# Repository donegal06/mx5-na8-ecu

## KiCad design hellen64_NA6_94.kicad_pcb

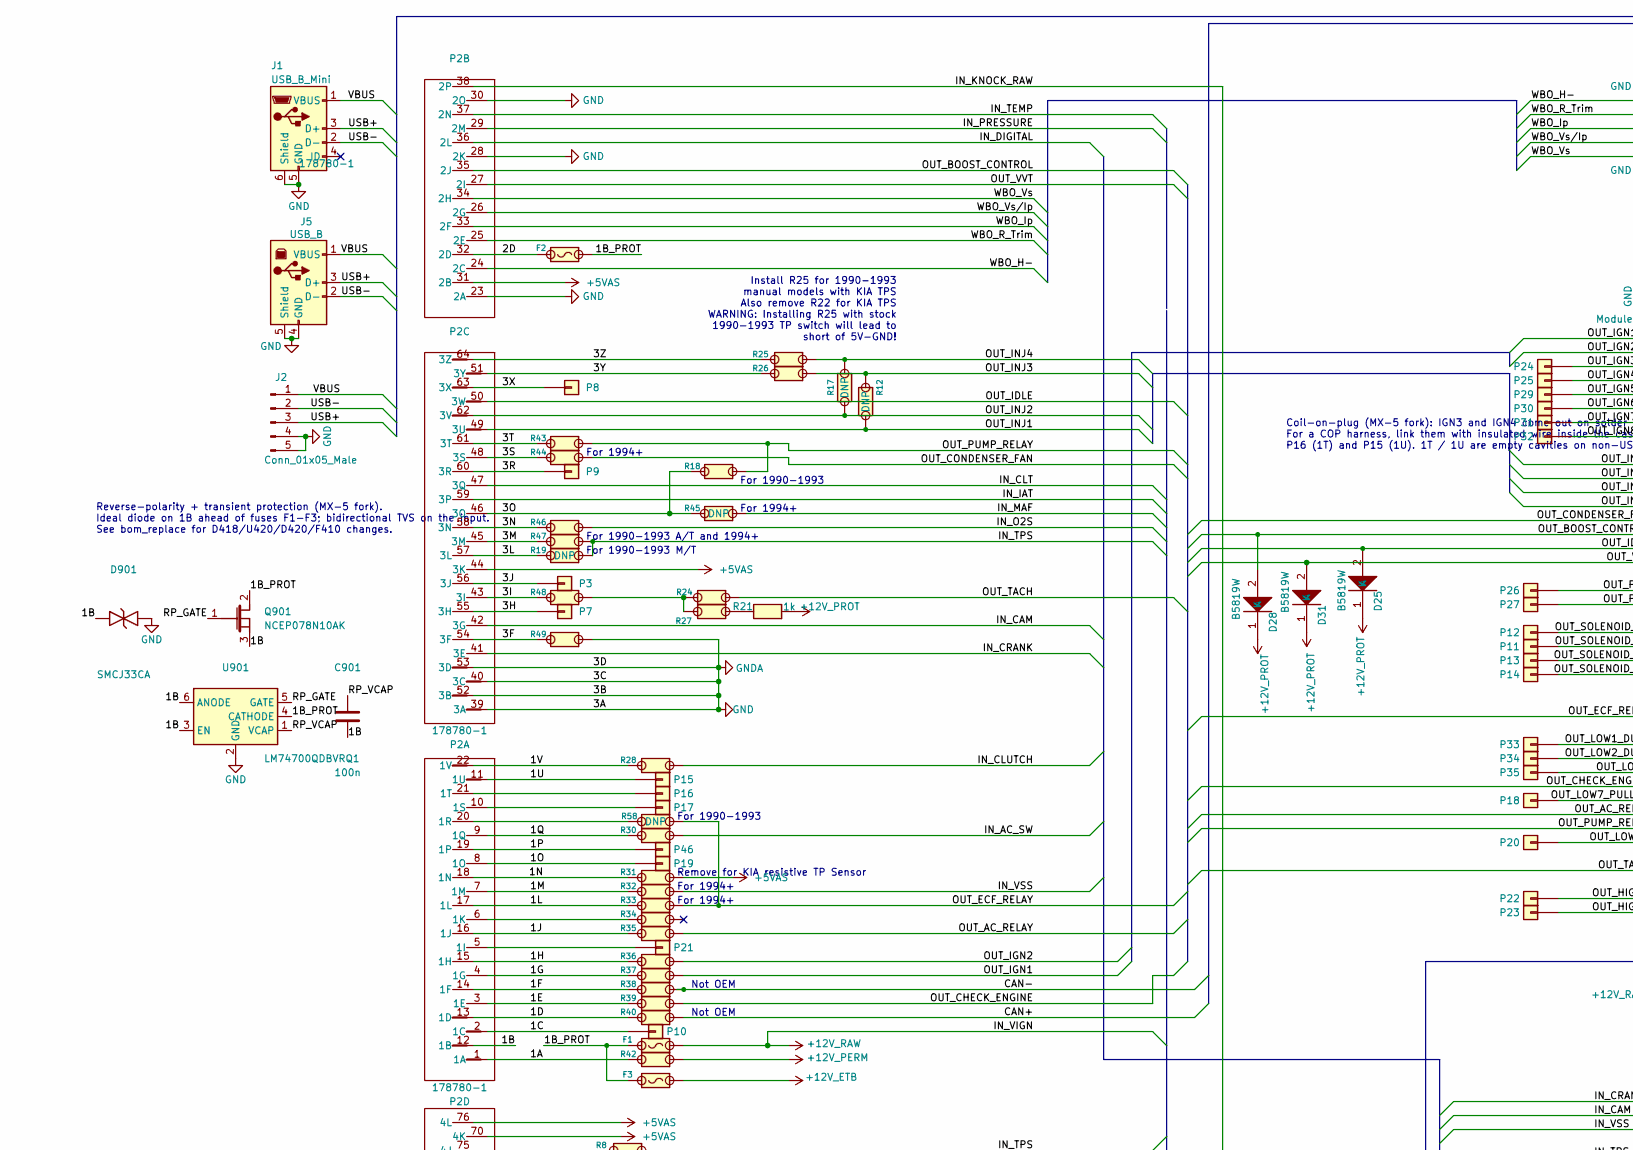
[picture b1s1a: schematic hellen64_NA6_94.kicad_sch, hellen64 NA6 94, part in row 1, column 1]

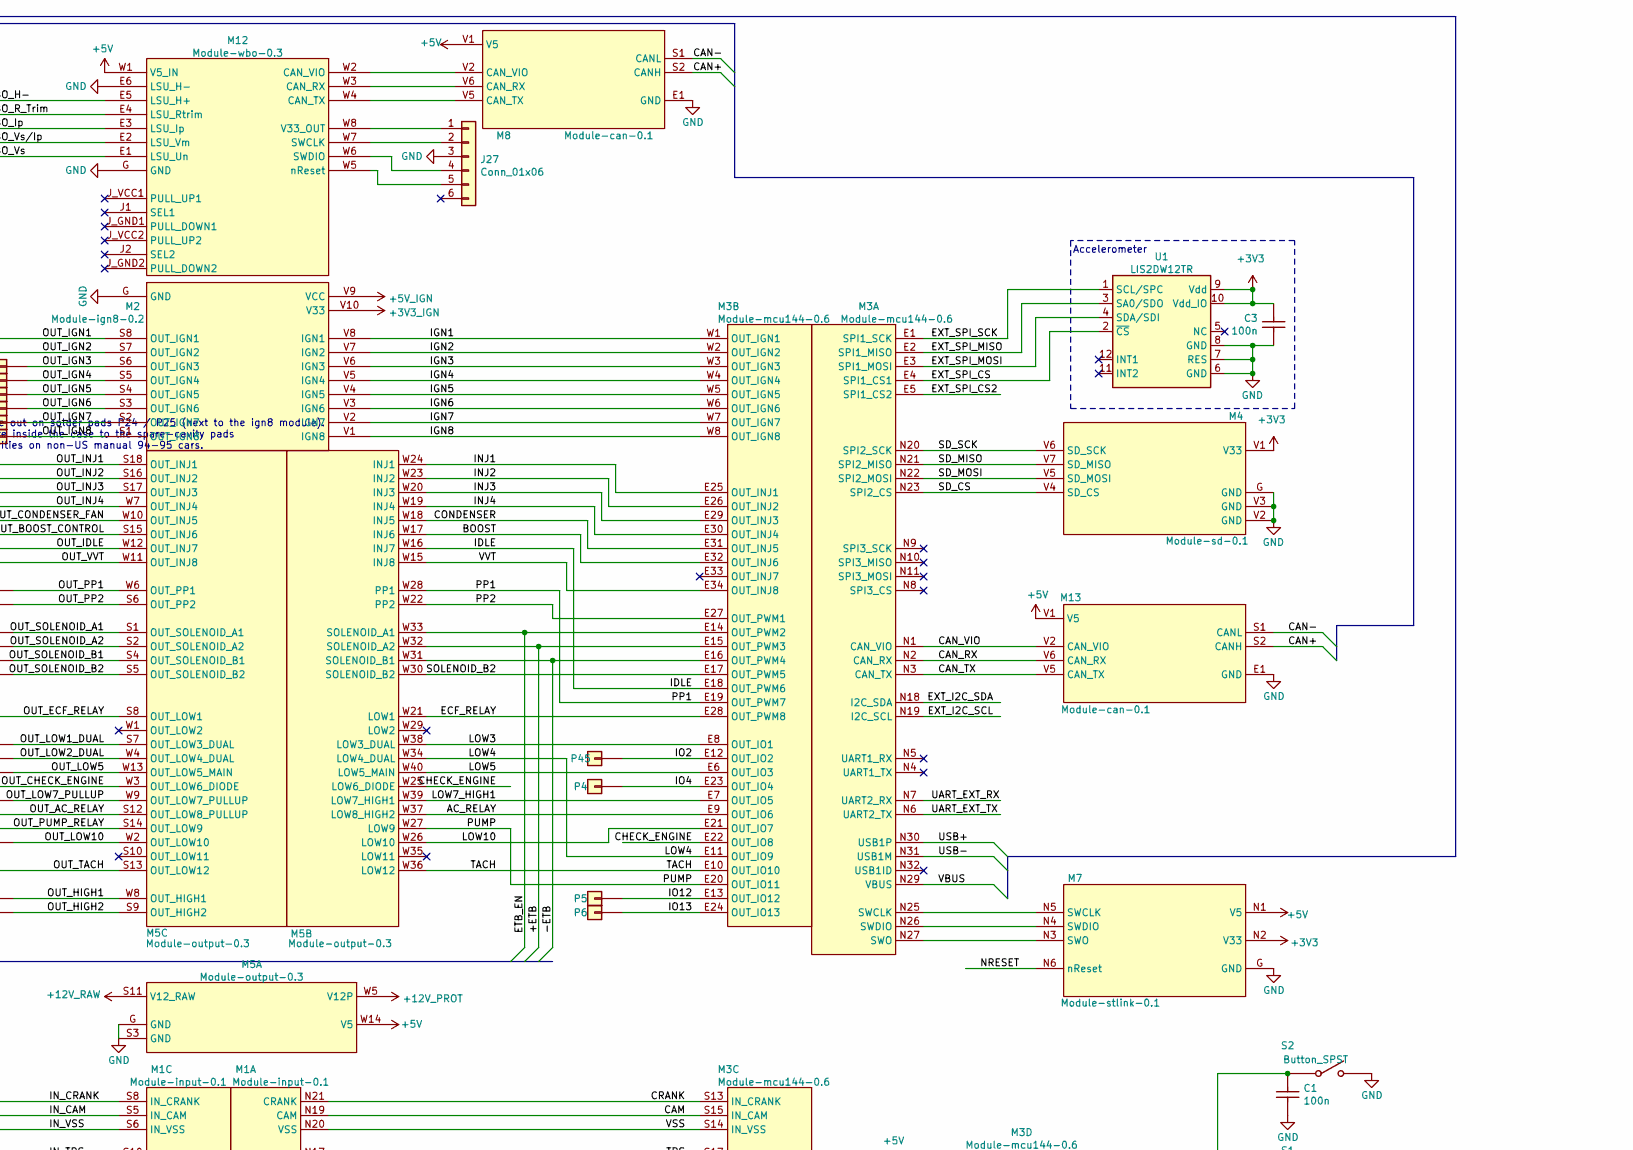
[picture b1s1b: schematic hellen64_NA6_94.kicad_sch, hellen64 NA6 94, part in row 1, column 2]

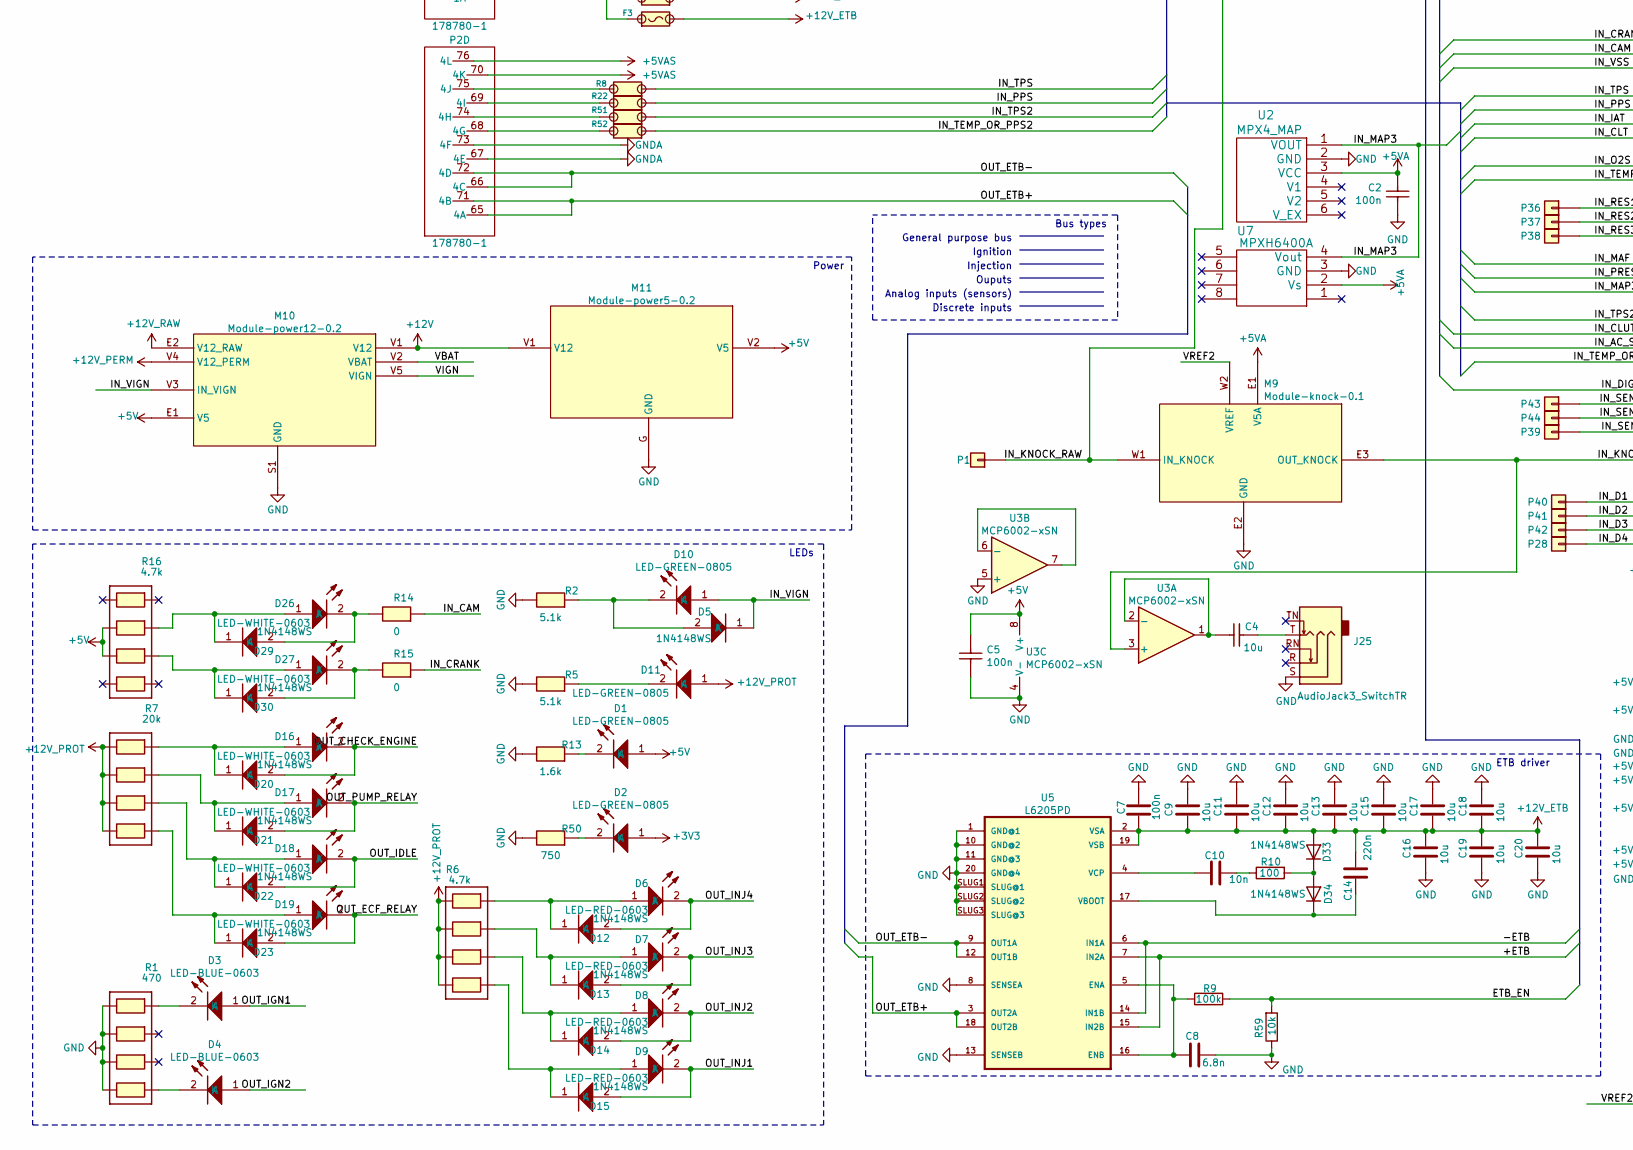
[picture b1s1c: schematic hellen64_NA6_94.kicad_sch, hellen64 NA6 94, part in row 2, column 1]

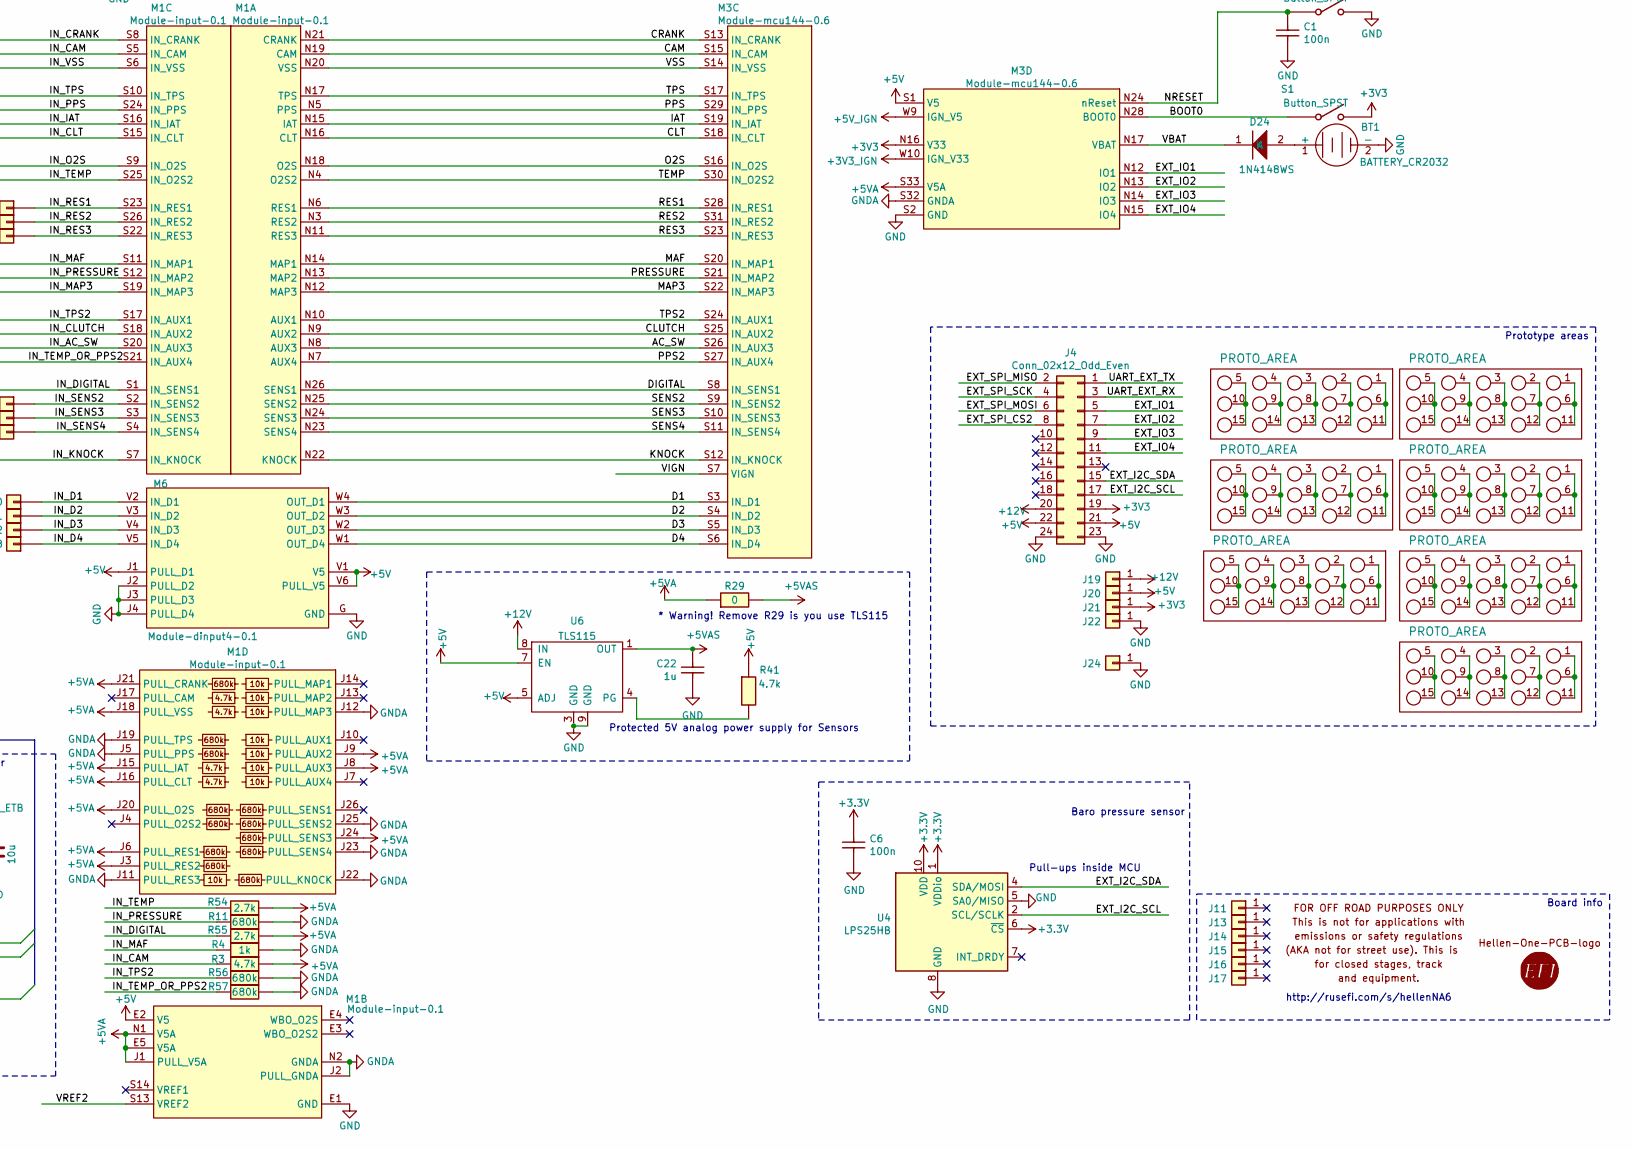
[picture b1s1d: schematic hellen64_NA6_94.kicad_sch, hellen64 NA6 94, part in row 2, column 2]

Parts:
BT1: BATTERY_CR2032; BatteryHolder_Keystone_1060_1x2032; LCSC C70377
C1, C2, C3, C5, C6, C7, C901: 100n; C0603; LCSC C14663
C4: 10u; C0603; LCSC C19702
C8: 6.8n; C0603; LCSC C1631
C9, C11, C12, C13, C15, C16, C17, C18, C19, C20: 10u; C0805; LCSC C15850
C10: 10n; C0603; LCSC C57112
C14: 220n; C0603; LCSC C21120
C22: 1u; C0603; LCSC C15849
D1, D2, D10, D11: LED-GREEN-0805; LED-0805; LCSC C2297
D3, D4: LED-BLUE-0603; LED-0603; LCSC C72041
D5, D12, D13, D14, D15, D20, D21, D22, D23, D24, D29, D30, D33, D34: 1N4148WS; SOD-323; LCSC C2128
D6, D7, D8, D9: LED-RED-0603; LED-0603; LCSC C2286
D16, D17, D18, D19, D26, D27: LED-WHITE-0603; LED-0603; LCSC C2290
D25, D28, D31: B5819W; SOD-123; LCSC C8598
D901: SMCJ33CA; D_SMC; LCSC C699040
F1, F2, F3: Fuse-Pad-Pad; PAD-1206-PAD; LCSC C182446
G1, G3: LOGO
G2: DISCLAIMER; Off_Road_Disclaimer
G4, G5, G6, G7, G9, G11, G12: PROTO_AREA
J1: USB_B_Mini; USB-MINI-B-VERTICAL; LCSC C13453
J2: Conn_01x05_Male; Molex_SPOX_5267-05A_1x05_P2.50mm_Vertical
J4: Conn_02x12_Odd_Even; PinHeader_2x12_P2.54mm_Vertical
J5: USB_B; LCSC C46392
J11, J13, J14, J15, J16, J17: Conn_01x01; MountingHole_4.5mm_Pad
J19, J20, J21, J22, J24: Conn_01x01; TestPoint_Pad_D2.0mm
J25: AudioJack3_SwitchTR; Jack_3.5mm_PJ-3250-5A; LCSC C165947
J27: Conn_01x06; PinHeader_1x06_P2.54mm_Vertical
M1: Module-input-0.1; input
M2: Module-ign8-0.2; ign8
M3: Module-mcu144-0.6; mcu
M4: Module-sd-0.1; sd
M5: Module-output-0.3; output
M6: Module-dinput4-0.1; dinput4
M7: Module-stlink-0.1; stlink
M8, M13: Module-can-0.1; can
M9: Module-knock-0.1; knock
M10: Module-power12-0.2; power12
M11: Module-power5-0.2; power5
M12: Module-wbo-0.3; wbo
P1, P3, P4, P5, P6, P7, P8, P9, P10, P11, P12, P13, P14, P15, P16, P17, P18, P19, P20, P21, P22, P23, P24, P25, P26, P27, P28, P29, P30, P31, P32, P33, P34, P35, P36, P37, P38, P39, P40, P41, P42, P43, P44, P45, P46: Pad; PAD-TH
P2: 178780-1
Q901: NCEP078N10AK; TO-252-2; LCSC C2686699
R1: 470; R0603-4; LCSC C25510
R2, R5: 5.1k; R0603; LCSC C23186
R3, R41: 4.7k; R0603; LCSC C23162
R4, R21: 1k; R0603; LCSC C21190
R6, R16: 4.7k; R0603-4; LCSC C1980
R7: 20k; R0603-4; LCSC C12004
R8, R18, R22, R24, R25, R26, R27, R28, R30, R31, R32, R33, R34, R35, R36, R37, R38, R39, R40, R42, R43, R44, R46, R47, R48, R49, R51, R52: Jumper-Pad-Pad; PAD-0805-PAD; LCSC C17477
R9: 100k; R0603; LCSC C25803
R10: 100; R0603; LCSC C22775
R11, R56, R57: 680k; R0603; LCSC C25822
R12, R17, R19, R45, R58: Jumper-Pad-Pad; PAD-0805-PAD
R13: 1.6k; R0603; LCSC C22847
R14, R15: 0; R0603; LCSC C21189
R29: SMD1206B035TF/16; R1206; LCSC C269114
R50: 750; R0603; LCSC C23241
R54, R55: 2.7k; R0603; LCSC C13167
R59: 10k; R0603; LCSC C25804
S1, S2: Button_SPST; SMD-2_2.9x3.9x1.7; LCSC C115357
U1: LIS2DW12TR; LGA-12_2x2mm_P0.5mm; LCSC C189624
U2: MPX4_MAP; MPX-4_MAP
U3: MCP6002-xSN; SOIC-8_3.9x4.9mm_P1.27mm; LCSC C7377
U4: LPS25HB; ST_HLGA-10_2.5x2.5mm_P0.6mm_LayoutBorder3x2y; LCSC C87898
U5: L6205PD; SO20POWER; LCSC C36543
U6: TLS115; PG-DSO-8-43; LCSC C540242
U7: MPXH6400A; MPXH6400A-SSOP8; LCSC C511770
U901: LM74700QDBVRQ1; SOT-23-6; LCSC C2941042

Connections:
+3V3_IGN: M2.V10 (V33), M3.W10 (IGN_V33)
+5V: C5.2, D1.1 (A), J4.21, J4.22, J20.1, M1.E2 (V5), M3.S1 (V5), M5.W14 (V5), M6.J1 (PULL_D1), M6.V1 (V5), M6.V6 (PULL_V5), M7.N1 (V5), M8.V1 (V5), M10.E1 (V5), M11.V2 (V5), M12.W1 (V5_IN), M13.V1 (V5), R16.2, R16.3, R41.1, U3.8 (V+), U6.5 (ADJ), U6.7 (EN)
+5VA: C2.2, M1.E5 (V5A), M1.J1 (PULL_V5A), M1.J3 (PULL_RES2), M1.J6 (PULL_RES1), M1.J8 (PULL_AUX3), M1.J9 (PULL_AUX2), M1.J15 (PULL_IAT), M1.J16 (PULL_CLT), M1.J18 (PULL_VSS), M1.J20 (PULL_O2S), M1.J21 (PULL_CRANK), M1.J24 (PULL_SENS3), M1.N1 (V5A), M3.S33 (V5A), M9.E1 (V5A), R3.1, R29.1, R54.2, R55.2, U2.3 (VCC), U7.2 (Vs)
+5VAS: C22.2, P2.31 (2B), P2.44 (3K), P2.70 (4K), P2.76 (4L), R29.2, R31.1, U6.1 (OUT)
+5V_IGN: M2.V9 (VCC), M3.W9 (IGN_V5)
+12V: J4.20, J19.1, M10.V1 (V12), M11.V1 (V12), U6.8 (IN)
+12V_ETB: C7.2, C9.1, C11.1, C12.1, C13.1, C14.1, C15.1, C16.2, C17.1, C18.1, C19.2, C20.2, D33.2 (A), F3.2, U5.2 (VSA), U5.19 (VSB)
+12V_PERM: M10.V4 (V12_PERM), R42.1
+12V_PROT: D11.1 (A), D25.1 (K), D28.1 (K), D31.1 (K), M5.W5 (V12P), R6.1, R6.2, R6.3, R6.4, R7.1, R7.2, R7.3, R7.4, R21.1
+12V_RAW: D5.1 (K), D10.1 (A), F1.2, M5.S11 (V12_RAW), M10.E2 (V12_RAW), M10.V3 (IN_VIGN)
/1A: P2.1 (1A), R42.2
/1B: C901.2, D901.1 (A1), P2.12 (1B), Q901.3 (S), U901.3 (EN), U901.6 (ANODE)
/1B_PROT: F1.1, F2.2, F3.1, Q901.2 (D), U901.4 (CATHODE)
/1C: P2.2 (1C), P10.1
/1D: P2.13 (1D), R40.2
/1E: P2.3 (1E), R39.2
/1F: P2.14 (1F), R38.2
/1G: P2.4 (1G), R37.2
/1H: P2.15 (1H), R36.2
/1J: P2.16 (1J), R35.2
/1L: P2.17 (1L), R33.2
/1M: P2.7 (1M), R32.2
/1N: P2.18 (1N), R31.2
/1O: P2.8 (1O), P19.1
/1P: P2.19 (1P), P46.1
/1Q: P2.9 (1Q), R30.2
/1U: P2.11 (1U), P15.1
/1V: P2.22 (1V), R28.2
/2D: F2.1, P2.32 (2D)
/3F: P2.54 (3F), R49.2
/3H: P2.55 (3H), P7.1
/3I: P2.43 (3I), R48.2
/3J: P2.56 (3J), P3.1
/3L: P2.57 (3L), R19.2
/3M: P2.45 (3M), R47.2
/3N: P2.58 (3N), R46.2
/3O: P2.46 (3O), R18.2, R45.2
/3R: P2.60 (3R), P9.1
/3S: P2.48 (3S), R44.2
/3T: P2.61 (3T), R43.2
/3X: P2.63 (3X), P8.1
/3Y: P2.51 (3Y), R26.2
/3Z: P2.64 (3Z), R25.2
/+ETB: M3.E15 (OUT_PWM3), M5.W32 (SOLENOID_A2), U5.7 (IN2A), U5.15 (IN2B)
/-ETB: M3.E16 (OUT_PWM4), M5.W31 (SOLENOID_B1), U5.6 (IN1A), U5.14 (IN1B)
/AC_RELAY: M3.E9 (OUT_IO6), M5.W37 (LOW8_HIGH2)
/AC_SW: M1.N8 (AUX3), M3.S26 (IN_AUX3)
/BOOST: M3.E32 (OUT_INJ6), M5.W17 (INJ6)
/BOOT0: M3.N28 (BOOT0), S1.1
/CAM: M1.N19 (CAM), M3.S15 (IN_CAM)
/CAN+: M8.S2 (CANH), M13.S2 (CANH), R40.1
/CAN-: M8.S1 (CANL), M13.S1 (CANL), R38.1
/CAN_RX: M3.N2 (CAN_RX), M13.V6 (CAN_RX)
/CAN_TX: M3.N3 (CAN_TX), M13.V5 (CAN_TX)
/CAN_VIO: M3.N1 (CAN_VIO), M13.V2 (CAN_VIO)
/CHECK_ENGINE: M3.E22 (OUT_IO8), M5.W25 (LOW6_DIODE)
/CLT: M1.N16 (CLT), M3.S18 (IN_CLT)
/CLUTCH: M1.N9 (AUX2), M3.S25 (IN_AUX2)
/CONDENSER: M3.E31 (OUT_INJ5), M5.W18 (INJ5)
/CRANK: M1.N21 (CRANK), M3.S13 (IN_CRANK)
/D1: M3.S3 (IN_D1), M6.W4 (OUT_D1)
/D2: M3.S4 (IN_D2), M6.W3 (OUT_D2)
/D3: M3.S5 (IN_D3), M6.W2 (OUT_D3)
/D4: M3.S6 (IN_D4), M6.W1 (OUT_D4)
/DIGITAL: M1.N26 (SENS1), M3.S8 (IN_SENS1)
/ECF_RELAY: M3.E28 (OUT_PWM8), M5.W21 (LOW1)
/ETB_EN: M3.E14 (OUT_PWM2), M5.W33 (SOLENOID_A1), R9.2, R59.2
/EXT_I2C_SCL: J4.17, M3.N19 (I2C_SCL), U4.2 (SCL/SCLK)
/EXT_I2C_SDA: J4.15, M3.N18 (I2C_SDA), U4.4 (SDA/MOSI)
/EXT_IO1: J4.5, M3.N12 (IO1)
/EXT_IO2: J4.7, M3.N13 (IO2)
/EXT_IO3: J4.9, M3.N14 (IO3)
/EXT_IO4: J4.11, M3.N15 (IO4)
/EXT_SPI_CS: M3.E4 (SPI1_CS1), U1.2 (~CS)
/EXT_SPI_CS2: J4.8, M3.E5 (SPI1_CS2)
/EXT_SPI_MISO: J4.2, M3.E2 (SPI1_MISO), U1.3 (SA0/SDO)
/EXT_SPI_MOSI: J4.6, M3.E3 (SPI1_MOSI), U1.4 (SDA/SDI)
/EXT_SPI_SCK: J4.4, M3.E1 (SPI1_SCK), U1.1 (SCL/SPC)
/IAT: M1.N15 (IAT), M3.S19 (IN_IAT)
/IDLE: M3.E18 (OUT_PWM6), M5.W16 (INJ7)
/IGN1: M2.V8 (IGN1), M3.W1 (OUT_IGN1)
/IGN2: M2.V7 (IGN2), M3.W2 (OUT_IGN2)
/IGN3: M2.V6 (IGN3), M3.W3 (OUT_IGN3)
/IGN4: M2.V5 (IGN4), M3.W4 (OUT_IGN4)
/IGN5: M2.V4 (IGN5), M3.W5 (OUT_IGN5)
/IGN6: M2.V3 (IGN6), M3.W6 (OUT_IGN6)
/IGN7: M2.V2 (IGN7), M3.W7 (OUT_IGN7)
/IGN8: M2.V1 (IGN8), M3.W8 (OUT_IGN8)
/INJ1: M3.E25 (OUT_INJ1), M5.W24 (INJ1)
/INJ2: M3.E26 (OUT_INJ2), M5.W23 (INJ2)
/INJ3: M3.E29 (OUT_INJ3), M5.W20 (INJ3)
/INJ4: M3.E30 (OUT_INJ4), M5.W19 (INJ4)
/IN_AC_SW: M1.S20 (IN_AUX3), R30.1
/IN_CAM: M1.S5 (IN_CAM), P2.42 (3G), R3.2, R14.1
/IN_CLT: M1.S15 (IN_CLT), P2.47 (3Q)
/IN_CLUTCH: M1.S18 (IN_AUX2), R28.1
/IN_CRANK: M1.S8 (IN_CRANK), P2.41 (3E), R15.1
/IN_D1: M6.V2 (IN_D1), P40.1
/IN_D2: M6.V3 (IN_D2), P41.1
/IN_D3: M6.V4 (IN_D3), P42.1
/IN_D4: M6.V5 (IN_D4), P28.1
/IN_DIGITAL: M1.S1 (IN_SENS1), P2.36 (2L), R55.1
/IN_IAT: M1.S16 (IN_IAT), P2.59 (3P)
/IN_KNOCK: M1.S7 (IN_KNOCK), M9.E3 (OUT_KNOCK), U3.3 (+)
/IN_KNOCK_RAW: M9.W1 (IN_KNOCK), P1.1, P2.38 (2P)
/IN_MAF: M1.S11 (IN_MAP1), R4.1, R45.1
/IN_MAP3: M1.S19 (IN_MAP3), U2.1 (VOUT), U7.4 (Vout)
/IN_O2S: M1.S9 (IN_O2S), R46.1
/IN_PPS: M1.S24 (IN_PPS), R22.1
/IN_PRESSURE: M1.S12 (IN_MAP2), P2.29 (2M), R11.1
/IN_RES1: M1.S23 (IN_RES1), P36.1
/IN_RES2: M1.S26 (IN_RES2), P37.1
/IN_RES3: M1.S22 (IN_RES3), P38.1
/IN_SENS2: M1.S2 (IN_SENS2), P43.1
/IN_SENS3: M1.S3 (IN_SENS3), P44.1
/IN_SENS4: M1.S4 (IN_SENS4), P39.1
/IN_TEMP: M1.S25 (IN_O2S2), P2.37 (2N), R54.1
/IN_TEMP_OR_PPS2: M1.S21 (IN_AUX4), R52.1, R57.1
/IN_TPS: M1.S10 (IN_TPS), R8.1, R19.1, R47.1
/IN_TPS2: M1.S17 (IN_AUX1), R51.1, R56.1
/IN_VSS: M1.S6 (IN_VSS), R32.1
/IO2: M3.E12 (OUT_IO2), P45.1
/IO4: M3.E23 (OUT_IO4), P4.1
/IO12: M3.E13 (OUT_IO12), P5.1
/IO13: M3.E24 (OUT_IO13), P6.1
/KNOCK: M1.N22 (KNOCK), M3.S12 (IN_KNOCK)
/LOW3: M3.E8 (OUT_IO1), M5.W38 (LOW3_DUAL)
/LOW4: M3.E11 (OUT_IO9), M5.W34 (LOW4_DUAL)
/LOW5: M3.E6 (OUT_IO3), M5.W40 (LOW5_MAIN)
/LOW7_HIGH1: M3.E7 (OUT_IO5), M5.W39 (LOW7_HIGH1)
/LOW10: M3.E21 (OUT_IO7), M5.W26 (LOW10)
/MAF: M1.N14 (MAP1), M3.S20 (IN_MAP1)
/MAP3: M1.N12 (MAP3), M3.S22 (IN_MAP3)
/NRESET: C1.2, M3.N24 (nReset), M7.N6 (nReset), S2.1
/O2S: M1.N18 (O2S), M3.S16 (IN_O2S)
/OUT_AC_RELAY: M5.S12 (OUT_LOW8_PULLUP), R35.1
/OUT_BOOST_CONTROL: D28.2 (A), M5.S15 (OUT_INJ6), P2.35 (2J)
/OUT_CHECK_ENGINE: D16.2 (K), D20.2 (A), M5.W3 (OUT_LOW6_DIODE), R39.1
/OUT_CONDENSER_FAN: M5.W10 (OUT_INJ5), R44.1
/OUT_ECF_RELAY: D19.2 (K), D23.2 (A), M5.S8 (OUT_LOW1), R33.1, R58.1
/OUT_ETB+: P2.65 (4A), P2.71 (4B), U5.3 (OUT2A), U5.18 (OUT2B)
/OUT_ETB-: P2.66 (4C), P2.72 (4D), U5.9 (OUT1A), U5.12 (OUT1B)
/OUT_HIGH1: M5.W8 (OUT_HIGH1), P22.1
/OUT_HIGH2: M5.S9 (OUT_HIGH2), P23.1
/OUT_IDLE: D18.2 (K), D22.2 (A), D25.2 (A), M5.W12 (OUT_INJ7), P2.50 (3W)
/OUT_IGN1: D3.1 (A), M2.S8 (OUT_IGN1), R37.1
/OUT_IGN2: D4.1 (A), M2.S7 (OUT_IGN2), R36.1
/OUT_IGN3: M2.S6 (OUT_IGN3), P24.1
/OUT_IGN4: M2.S5 (OUT_IGN4), P25.1
/OUT_IGN5: M2.S4 (OUT_IGN5), P29.1
/OUT_IGN6: M2.S3 (OUT_IGN6), P30.1
/OUT_IGN7: M2.S2 (OUT_IGN7), P31.1
/OUT_IGN8: M2.S1 (OUT_IGN8), P32.1
/OUT_INJ1: D9.2 (K), D15.2 (A), M5.S18 (OUT_INJ1), P2.49 (3U), R12.2
/OUT_INJ2: D8.2 (K), D14.2 (A), M5.S16 (OUT_INJ2), P2.62 (3V), R17.2
/OUT_INJ3: D7.2 (K), D13.2 (A), M5.S17 (OUT_INJ3), R12.1, R26.1
/OUT_INJ4: D6.2 (K), D12.2 (A), M5.W7 (OUT_INJ4), R17.1, R25.1
/OUT_LOW1_DUAL: M5.S7 (OUT_LOW3_DUAL), P33.1
/OUT_LOW2_DUAL: M5.W4 (OUT_LOW4_DUAL), P34.1
/OUT_LOW5: M5.W13 (OUT_LOW5_MAIN), P35.1
/OUT_LOW7_PULLUP: M5.W9 (OUT_LOW7_PULLUP), P18.1
/OUT_LOW10: M5.W2 (OUT_LOW10), P20.1
/OUT_PP1: M5.W6 (OUT_PP1), P26.1
/OUT_PP2: M5.S6 (OUT_PP2), P27.1
/OUT_PUMP_RELAY: D17.2 (K), D21.2 (A), M5.S14 (OUT_LOW9), R18.1, R43.1
/OUT_SOLENOID_A1: M5.S1 (OUT_SOLENOID_A1), P12.1
/OUT_SOLENOID_A2: M5.S2 (OUT_SOLENOID_A2), P11.1
/OUT_SOLENOID_B1: M5.S4 (OUT_SOLENOID_B1), P13.1
/OUT_SOLENOID_B2: M5.S5 (OUT_SOLENOID_B2), P14.1
/OUT_TACH: M5.S13 (OUT_LOW12), R24.1
/OUT_VVT: D31.2 (A), M5.W11 (OUT_INJ8), P2.27 (2I)
/PP1: M3.E19 (OUT_PWM7), M5.W28 (PP1)
/PP2: M3.E27 (OUT_PWM1), M5.W22 (PP2)
/PPS: M1.N5 (PPS), M3.S29 (IN_PPS)
/PPS2: M1.N7 (AUX4), M3.S27 (IN_AUX4)
/PRESSURE: M1.N13 (MAP2), M3.S21 (IN_MAP2)
/PUMP: M3.E20 (OUT_IO11), M5.W27 (LOW9)
/RES1: M1.N6 (RES1), M3.S28 (IN_RES1)
/RES2: M1.N3 (RES2), M3.S31 (IN_RES2)
/RES3: M1.N11 (RES3), M3.S23 (IN_RES3)
/RP_GATE: Q901.1 (G), U901.5 (GATE)
/RP_VCAP: C901.1, U901.1 (VCAP)
/SD_CS: M3.N23 (SPI2_CS), M4.V4 (SD_CS)
/SD_MISO: M3.N21 (SPI2_MISO), M4.V7 (SD_MISO)
/SD_MOSI: M3.N22 (SPI2_MOSI), M4.V5 (SD_MOSI)
/SD_SCK: M3.N20 (SPI2_SCK), M4.V6 (SD_SCK)
/SENS2: M1.N25 (SENS2), M3.S9 (IN_SENS2)
/SENS3: M1.N24 (SENS3), M3.S10 (IN_SENS3)
/SENS4: M1.N23 (SENS4), M3.S11 (IN_SENS4)
/SOLENOID_B2: M3.E17 (OUT_PWM5), M5.W30 (SOLENOID_B2)
/TACH: M3.E10 (OUT_IO10), M5.W36 (LOW12)
/TEMP: M1.N4 (O2S2), M3.S30 (IN_O2S2)
/TPS: M1.N17 (TPS), M3.S17 (IN_TPS)
/TPS2: M1.N10 (AUX1), M3.S24 (IN_AUX1)
/UART_EXT_RX: J4.3, M3.N7 (UART2_RX)
/UART_EXT_TX: J4.1, M3.N6 (UART2_TX)
/USB+: J1.3 (D+), J2.3, J5.3 (D+), M3.N30 (USB1P)
/USB-: J1.2 (D-), J2.2, J5.2 (D-), M3.N31 (USB1M)
/VBAT: D24.1 (K), M3.N17 (VBAT), M10.V2 (VBAT)
/VBUS: J1.1 (VBUS), J2.1, J5.1 (VBUS), M3.N29 (VBUS)
/VIGN: M3.S7 (VIGN), M10.V5 (VIGN)
/VREF2: M1.S13 (VREF2), M9.W2 (VREF)
/VSS: M1.N20 (VSS), M3.S14 (IN_VSS)
/VVT: M3.E34 (OUT_INJ8), M5.W15 (INJ8)
/WBO_H-: M12.E5 (LSU_H+), P2.24 (2C)
/WBO_Ip: M12.E3 (LSU_Ip), P2.33 (2F)
/WBO_R_Trim: M12.E4 (LSU_Rtrim), P2.25 (2E)
/WBO_Vs: M12.E1 (LSU_Un), P2.34 (2H)
/WBO_Vs/Ip: M12.E2 (LSU_Vm), P2.26 (2G)
GND: BT1.2 (-), C1.1, C2.1, C3.1, C5.1, C6.1, C7.1, C8.2, C9.2, C11.2, C12.2, C13.2, C15.2, C16.1, C17.2, C18.2, C19.1, C20.1, C22.1, D901.2 (A2), J1.5 (GND), J1.6 (Shield), J2.4, J2.5, J4.23, J4.24, J5.4 (GND), J5.5 (Shield), J22.1, J24.1, J25.S, J27.3, M1.E1 (GND), M1.J2 (PULL_GNDA), M1.J5 (PULL_PPS), M1.J11 (PULL_RES3), M1.J12 (PULL_MAP3), M1.J19 (PULL_TPS), M1.J22 (PULL_KNOCK), M1.J23 (PULL_SENS4), M1.J25 (PULL_SENS2), M1.N2 (GNDA), M2.G (GND), M3.S2 (GND), M3.S32 (GNDA), M4.G (GND), M4.V2 (GND), M4.V3 (GND), M5.G (GND), M5.S3 (GND), M6.G (GND), M6.J2 (PULL_D2), M6.J3 (PULL_D3), M6.J4 (PULL_D4), M7.G (GND), M8.E1 (GND), M9.E2 (GND), M10.S1 (GND), M11.G (GND), M12.E6 (LSU_H-), M12.G (GND), M13.E1 (GND), P2.23 (2A), P2.28 (2K), P2.30 (2O), P2.39 (3A), P2.40 (3C), P2.52 (3B), P2.53 (3D), P2.67 (4E), P2.73 (4F), R1.1, R1.2, R1.3, R1.4, R2.2, R4.2, R5.2, R11.2, R13.2, R49.1, R50.2, R56.2, R57.2, R59.1, S2.2, U1.6 (GND), U1.7 (RES), U1.8 (GND), U2.2 (GND), U3.4 (V-), U3.5 (+), U4.3 (GND), U4.5 (SA0/MISO), U4.8 (GND), U4.9 (GND), U5.1 (GND@1), U5.8 (SENSEA), U5.10 (GND@2), U5.11 (GND@3), U5.13 (SENSEB), U5.20 (GND@4), U5.SLUG1 (SLUG@1), U5.SLUG2 (SLUG@2), U5.SLUG3 (SLUG@3), U6.3 (GND), U6.9 (GND), U7.3 (GND), U901.2 (GND)
unnamed: BT1.1 (+), D24.2 (A)
unnamed: C4.1, J25.T
unnamed: C4.2, U3.1, U3.2 (-)
unnamed: C8.1, R9.1, U5.5 (ENA), U5.16 (ENB)
unnamed: C10.1, R10.1
unnamed: C10.2, U5.4 (VCP)
unnamed: C14.2, D34.1 (K), U5.17 (VBOOT)
unnamed: D1.2 (K), R13.1
unnamed: D2.2 (K), R50.1
unnamed: D3.2 (K), R1.8
unnamed: D4.2 (K), R1.5
unnamed: D5.2 (A), D10.2 (K), R2.1
unnamed: D11.2 (K), R5.1
unnamed: D6.1 (A), D12.1 (K), R6.8
unnamed: D7.1 (A), D13.1 (K), R6.7
unnamed: D8.1 (A), D14.1 (K), R6.6
unnamed: D9.1 (A), D15.1 (K), R6.5
unnamed: D16.1 (A), D20.1 (K), R7.8
unnamed: D17.1 (A), D21.1 (K), R7.7
unnamed: D18.1 (A), D22.1 (K), R7.6
unnamed: D19.1 (A), D23.1 (K), R7.5
unnamed: D26.1 (A), D29.1 (K), R16.7
unnamed: D26.2 (K), D29.2 (A), R14.2
unnamed: D27.1 (A), D30.1 (K), R16.6
unnamed: D27.2 (K), D30.2 (A), R15.2
unnamed: D33.1 (K), D34.2 (A), R10.2
unnamed: G4.1, G4.6, G4.11
unnamed: G4.5, G4.10, G4.15
unnamed: G4.2, G4.7, G4.12
unnamed: G4.3, G4.8, G4.13
unnamed: G4.4, G4.9, G4.14
unnamed: G5.1, G5.6, G5.11
unnamed: G5.5, G5.10, G5.15
unnamed: G5.2, G5.7, G5.12
unnamed: G5.3, G5.8, G5.13
unnamed: G5.4, G5.9, G5.14
unnamed: G6.1, G6.6, G6.11
unnamed: G6.5, G6.10, G6.15
unnamed: G6.2, G6.7, G6.12
unnamed: G6.3, G6.8, G6.13
unnamed: G6.4, G6.9, G6.14
unnamed: G7.1, G7.6, G7.11
unnamed: G7.5, G7.10, G7.15
unnamed: G7.2, G7.7, G7.12
unnamed: G7.3, G7.8, G7.13
unnamed: G7.4, G7.9, G7.14
unnamed: G9.1, G9.6, G9.11
unnamed: G9.5, G9.10, G9.15
unnamed: G9.2, G9.7, G9.12
unnamed: G9.3, G9.8, G9.13
unnamed: G9.4, G9.9, G9.14
unnamed: G11.1, G11.6, G11.11
unnamed: G11.5, G11.10, G11.15
unnamed: G11.2, G11.7, G11.12
unnamed: G11.3, G11.8, G11.13
unnamed: G11.4, G11.9, G11.14
unnamed: G12.1, G12.6, G12.11
unnamed: G12.5, G12.10, G12.15
unnamed: G12.2, G12.7, G12.12
unnamed: G12.3, G12.8, G12.13
unnamed: G12.4, G12.9, G12.14
unnamed: J27.1, M12.W8 (V33_OUT)
unnamed: J27.2, M12.W7 (SWCLK)
unnamed: J27.4, M12.W6 (SWDIO)
unnamed: J27.5, M12.W5 (nReset)
unnamed: M3.N25 (SWCLK), M7.N5 (SWCLK)
unnamed: M3.N26 (SWDIO), M7.N4 (SWDIO)
unnamed: M3.N27 (SWO), M7.N3 (SWO)
unnamed: M8.V2 (CAN_VIO), M12.W2 (CAN_VIO)
unnamed: M8.V6 (CAN_RX), M12.W3 (CAN_RX)
unnamed: M8.V5 (CAN_TX), M12.W4 (CAN_TX)
unnamed: P2.5 (1I), P21.1
unnamed: P2.6 (1K), R34.2
unnamed: P2.20 (1R), R58.2
unnamed: P2.68 (4G), R52.2
unnamed: P2.69 (4I), R22.2
unnamed: P2.74 (4H), R51.2
unnamed: P2.75 (4J), R8.2
unnamed: P2.21 (1T), P16.1
unnamed: P2.10 (1S), P17.1
unnamed: R21.2, R27.2
unnamed: R24.2, R27.1, R48.1
unnamed: R41.2, U6.4 (PG)
unnamed: U3.6 (-), U3.7

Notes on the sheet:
For 1990-1993 A/T and 1994+
Injection
* Warning! Remove R29 is you use TLS115
For 1990-1993
Analog inputs (sensors)
Install R25 for 1990-1993 manual models with KIA TPS Also remove R22 for KIA TPS WARNING: Installing R25 with stock 1990-1993 TP switch will lead to short of 5V-GND!
For 1994+
Not OEM
Ignition
Ouputs
For 1994+
Accelerometer
For 1990-1993 M/T
For 1990-1993
Pull-ups inside MCU
Protected 5V analog power supply for Sensors
Prototype areas
ETB driver
Bus types
LEDs
http://rusefi.com/s/hellenNA6
Board info
Power
General purpose bus
Remove for KIA resistive TP Sensor
Baro pressure sensor
Discrete inputs
Reverse-polarity + transient protection (MX-5 fork). Ideal diode on 1B ahead of fuses F1-F3; bidirectional TVS on the input. See bom_replace for D418/U420/D420/F410 changes.
Coil-on-plug (MX-5 fork): IGN3 and IGN4 come out on solder pads P24 / P25 (next to the ign8 module). For a COP harness, link them with insulated wire inside the case to the spare-cavity pads P16 (1T) and P15 (1U). 1T / 1U are empty cavities on non-US manual 94-95 cars.

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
